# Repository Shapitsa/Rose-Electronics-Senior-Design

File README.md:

# Rose-Electronics-Senior-Design

## 2026-04-09

Debugging session.  Using "DMX Cat" test tool, which the Arduino
receiver using the Conceptinetics DMX library doesn't like.

References:

* Using [DMXcat](https://www.citytheatrical.com/products/electronics/other-electronic/dmxcat-multi-function-test-tool)
* Conceptinetics libraries in use _probably_ from here:  https://github.com/alfo/arduino-libraries

Using the o-scope we determined that the DMXcat is sending plausible DMX data,
at the std bit rate of 250kHz.  This looks superficially the same as data sent
by both the Arduino master Anna has and also the example from the DMXSerial
Arduino library.

The problem remains a mystery... will pick it up

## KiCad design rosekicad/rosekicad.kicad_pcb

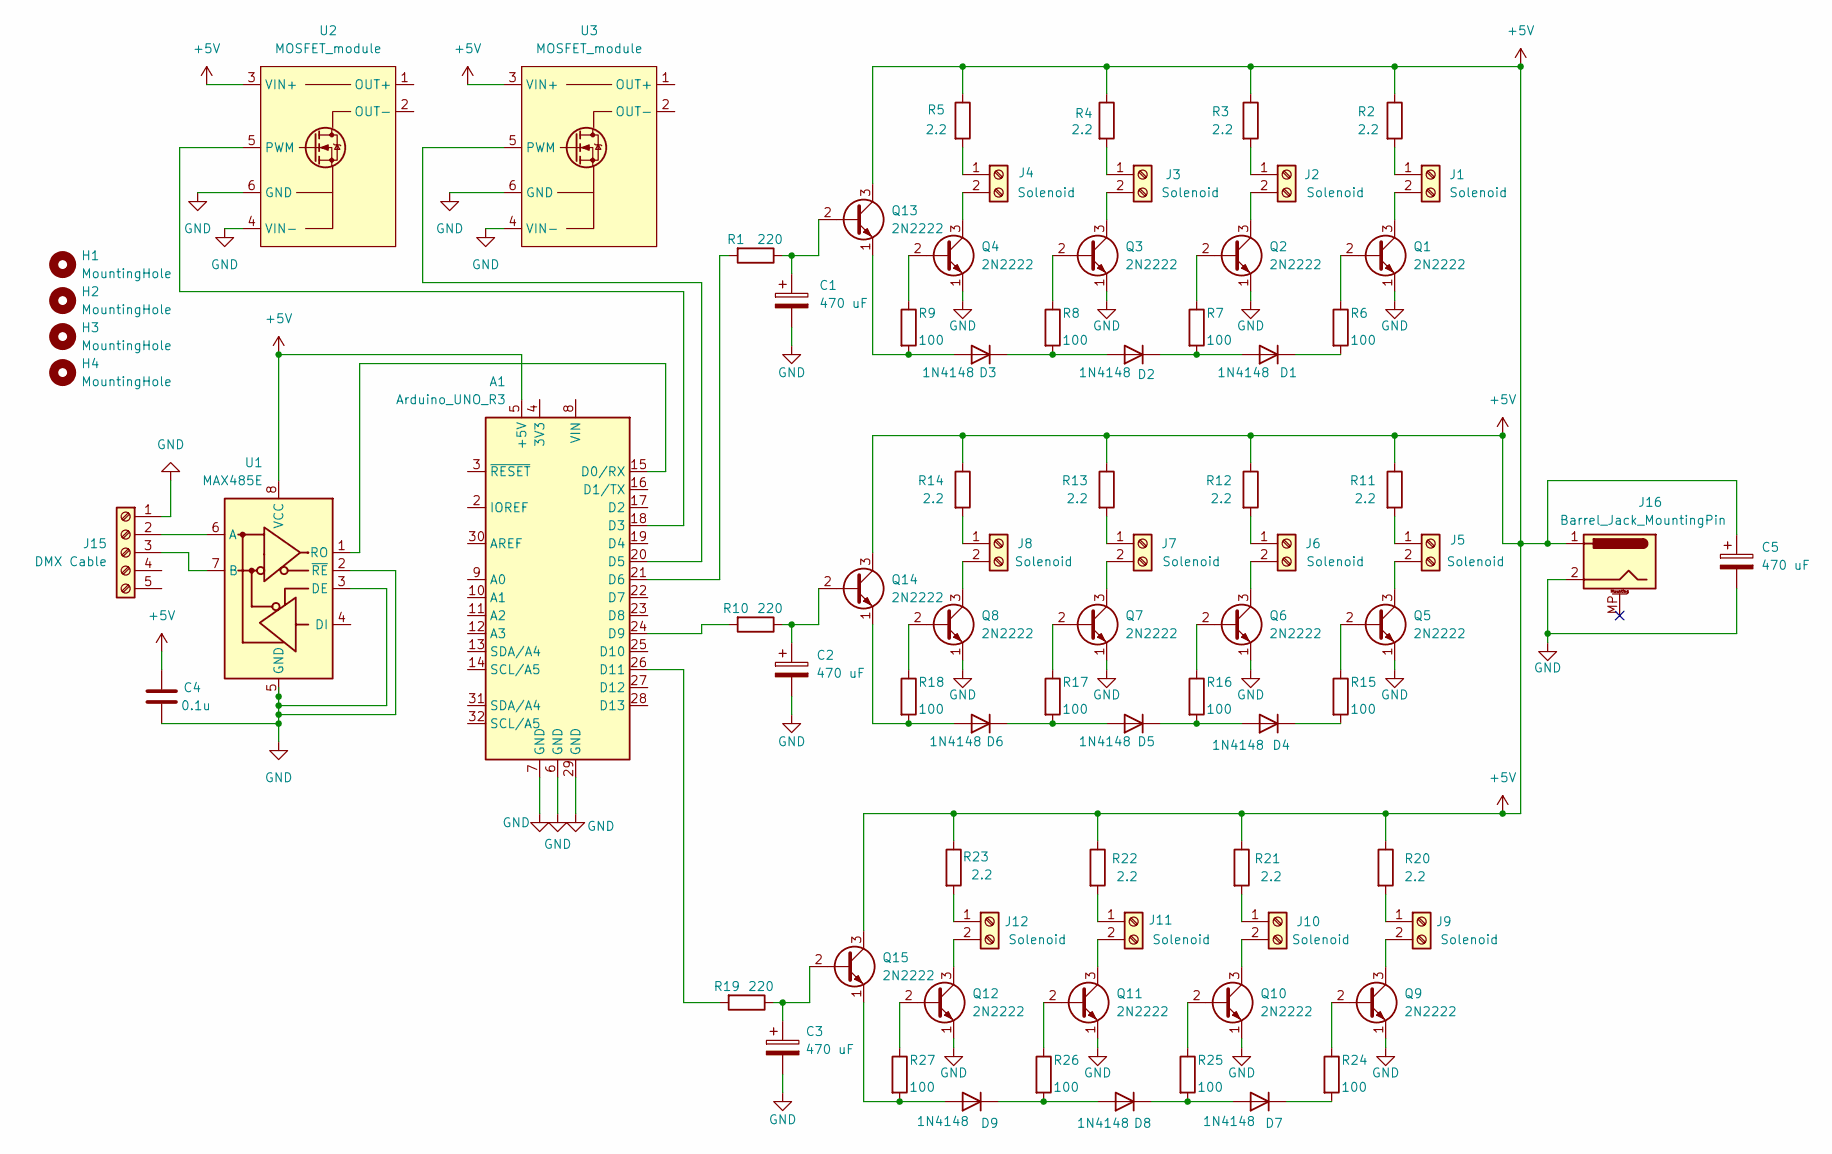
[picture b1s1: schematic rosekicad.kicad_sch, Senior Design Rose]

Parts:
A1: Arduino_UNO_R3
C1, C2, C3, C5: 470 uF; CP_Radial_D10.0mm_P3.80mm
C4: 0.1u; CP_Radial_D5.0mm_P2.00mm
D1, D2, D3, D4, D5, D6, D7, D8, D9: 1N4148; D_DO-35_SOD27_P7.62mm_Horizontal
H1, H2, H3, H4: MountingHole; MountingHole_4.5mm_Pad
J1, J2, J3, J4, J5, J6, J7, J8, J9, J10, J11, J12: Solenoid; TerminalBlock_MaiXu_MX126-5.0-02P_1x02_P5.00mm
J15: DMX Cable; TerminalBlock_MaiXu_MX126-5.0-05P_1x05_P5.00mm
J16: Barrel_Jack_MountingPin; BarrelJack_CUI_PJ-102AH_Horizontal
Q1, Q2, Q3, Q4, Q5, Q6, Q7, Q8, Q9, Q10, Q11, Q12, Q13, Q14, Q15: 2N2222; TO-92_Inline_Wide
R1, R10, R19: 220; R_Axial_DIN0207_L6.3mm_D2.5mm_P7.62mm_Horizontal
R2, R3, R4, R5, R11, R12, R13, R14, R20, R21, R22, R23: 2.2; R_Axial_DIN0414_L11.9mm_D4.5mm_P15.24mm_Horizontal
R6, R7, R8, R9, R15, R16, R17, R18, R24, R25, R26, R27: 100; R_Axial_DIN0207_L6.3mm_D2.5mm_P7.62mm_Horizontal
U1: MAX485E; MAX485_Module
U2, U3: MOSFET_module; MOSFET Switch Driver Module

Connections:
+5V: A1.5 (+5V), C4.1, C5.1, J16.1, Q13.3 (C), Q14.3 (C), Q15.3 (C), R2.1, R3.1, R4.1, R5.1, R11.1, R12.1, R13.1, R14.1, R20.1, R21.1, R22.1, R23.1, U1.8 (VCC), U2.3 (VIN+), U3.3 (VIN+)
GND: A1.6 (GND), A1.7 (GND), A1.29 (GND), C1.2, C2.2, C3.2, C4.2, C5.2, J15.1, J16.2, Q1.1 (E), Q2.1 (E), Q3.1 (E), Q4.1 (E), Q5.1 (E), Q6.1 (E), Q7.1 (E), Q8.1 (E), Q9.1 (E), Q10.1 (E), Q11.1 (E), Q12.1 (E), U1.2 (~RE), U1.3 (DE), U1.5 (GND), U2.4 (VIN-), U2.6 (GND), U3.4 (VIN-), U3.6 (GND)
unnamed: A1.15 (D0/RX), U1.1 (RO)
unnamed: A1.18 (D3), U2.5 (PWM)
unnamed: A1.20 (D5), U3.5 (PWM)
unnamed: A1.21 (D6), R1.2
unnamed: A1.24 (D9), R10.2
unnamed: A1.26 (D11), R19.2
unnamed: D1.2 (A), D2.1 (K), R7.2
unnamed: D1.1 (K), R6.2
unnamed: D2.2 (A), D3.1 (K), R8.2
unnamed: D3.2 (A), Q13.1 (E), R9.2
unnamed: D4.2 (A), D5.1 (K), R16.2
unnamed: D4.1 (K), R15.2
unnamed: D5.2 (A), D6.1 (K), R17.2
unnamed: D6.2 (A), Q14.1 (E), R18.2
unnamed: D7.2 (A), D8.1 (K), R25.2
unnamed: D7.1 (K), R24.2
unnamed: D8.2 (A), D9.1 (K), R26.2
unnamed: D9.2 (A), Q15.1 (E), R27.2
unnamed: J1.1, R2.2
unnamed: J1.2, Q1.3 (C)
unnamed: J2.1, R3.2
unnamed: J2.2, Q2.3 (C)
unnamed: J3.1, R4.2
unnamed: J3.2, Q3.3 (C)
unnamed: J4.1, R5.2
unnamed: J4.2, Q4.3 (C)
unnamed: J5.1, R11.2
unnamed: J5.2, Q5.3 (C)
unnamed: J6.1, R12.2
unnamed: J6.2, Q6.3 (C)
unnamed: J7.1, R13.2
unnamed: J7.2, Q7.3 (C)
unnamed: J8.1, R14.2
unnamed: J8.2, Q8.3 (C)
unnamed: J9.1, R20.2
unnamed: J9.2, Q9.3 (C)
unnamed: J10.1, R21.2
unnamed: J10.2, Q10.3 (C)
unnamed: J11.1, R22.2
unnamed: J11.2, Q11.3 (C)
unnamed: J12.1, R23.2
unnamed: J12.2, Q12.3 (C)
unnamed: J15.2, U1.6 (A)
unnamed: J15.3, U1.7 (B)
unnamed: Q1.2 (B), R6.1
unnamed: Q2.2 (B), R7.1
unnamed: Q3.2 (B), R8.1
unnamed: Q4.2 (B), R9.1
unnamed: Q5.2 (B), R15.1
unnamed: Q6.2 (B), R16.1
unnamed: Q7.2 (B), R17.1
unnamed: Q8.2 (B), R18.1
unnamed: Q9.2 (B), R24.1
unnamed: Q10.2 (B), R25.1
unnamed: Q11.2 (B), R26.1
unnamed: Q12.2 (B), R27.1
unnamed: C1.1, Q13.2 (B), R1.1
unnamed: C2.1, Q14.2 (B), R10.1
unnamed: C3.1, Q15.2 (B), R19.1

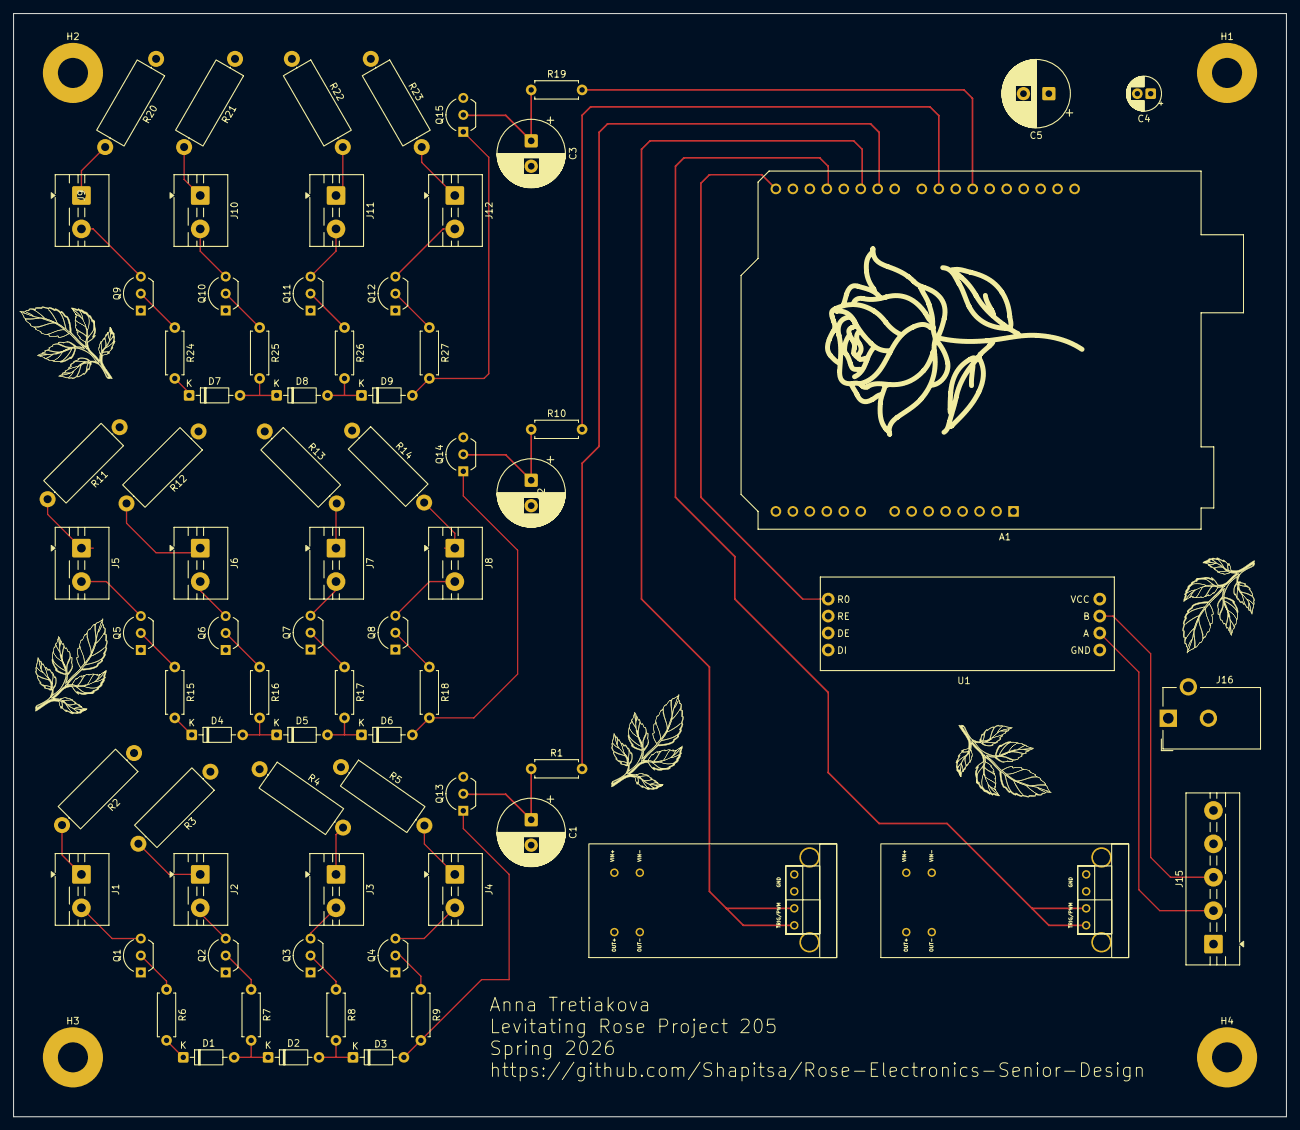
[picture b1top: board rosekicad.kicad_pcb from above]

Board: 4 copper layers, 190.5 x 165.1 mm, 78 parts (0 on the bottom side), 61 nets.

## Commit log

2026-01-22 start kicad
2026-01-22 first upload test
2026-01-24 updated scheatic
2026-01-24 updated footprints
2026-01-24 pcd one
2026-01-26 pcd built
2026-01-26 added footprint
2026-01-27 updated pcb
2026-01-28 Added four layers
2026-01-28 mounting holes
2026-01-29 finalized pcb main
2026-01-29 added silkscreen graphics
2026-02-02 gerber file
2026-02-24 mosfets added
2026-03-02 final
2026-04-09 Add software as of 4/8/26
2026-04-09 notes, move roseFinal to folder
2026-04-30 Add files via upload
    Final Arduino code
2026-04-30 Final Report
